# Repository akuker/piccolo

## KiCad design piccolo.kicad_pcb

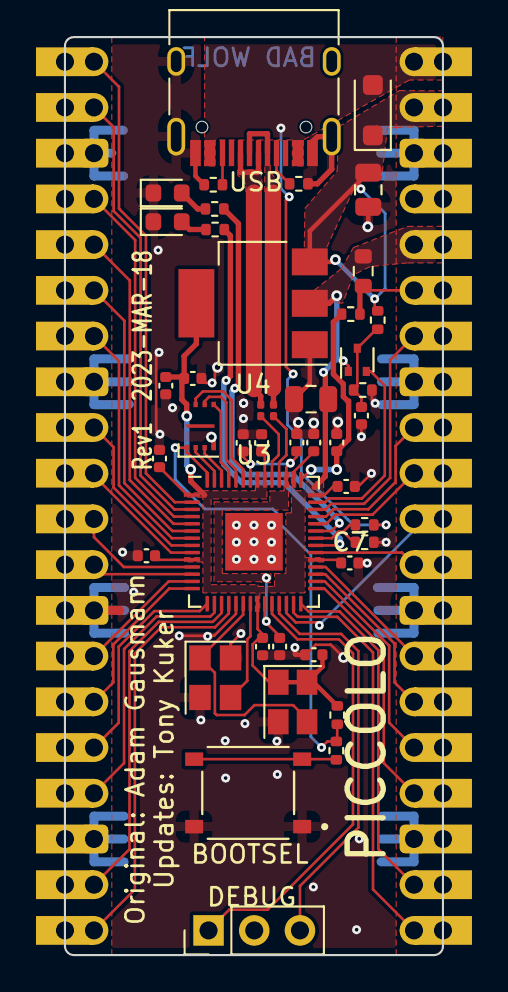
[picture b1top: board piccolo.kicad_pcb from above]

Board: 2 copper layers, 21.0 x 51.0 mm, 44 parts (0 on the bottom side), 58 nets.

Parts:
C1, C12, C14, C16: 2.2u 6.3V; C_0402_1005Metric
C2, C5, C7, C8, C9, C10, C11, C13, C15, C17: 100n 6.3V; C_0402_1005Metric
C3: 1n 25V; C_0402_1005Metric
C4, C6: 10u 6.3V; C_0805_2012Metric
D1: MBR120VLSFT1G; D_SOD-123F
D2: Green; LED_0603_1608Metric
D3: Red; LED_0603_1608Metric
J1: USB_C_Receptacle_USB2.0; USB_C_Receptacle_HRO_TYPE-C-31-M-12
J2: CON_PICO_40W; RaspberryPi_Pico_OutlineAndPads
J3: Debug; PinHeader_1x03_P2.54mm_Vertical
Q1: DMG1012T; SOT-523
R1: NO-FIT; R_0402_1005Metric
R2: 1k; R_0402_1005Metric
R3, R4: 5.1k; R_0402_1005Metric
R5: 5.6k; R_0402_1005Metric
R6: 10k; R_0402_1005Metric
R7: 200k; R_0402_1005Metric
R8: 100k; R_0402_1005Metric
R10, R11: 27R; R_0201_0603Metric
R12: 200R; R_0603_1608Metric
R13: 1R; R_0402_1005Metric
R14, R15: 470R; R_0402_1005Metric
SW2: TS-1187A-B-A-B; SW_TS-1187A-B-A-B
U1: W25Q16JVUXIQ; USON-8-1EP_3x2mm_P0.5mm_EP0.2x1.6mm
U3: RP2040; QFN-56-1EP_7x7mm_P0.4mm_EP3.2x3.2mm
U4: AMS1117-3.3; SOT-223-3_TabPin2
X1: SIT1602AI-22-33E-12.000000; Crystal_SMD_SeikoEpson_TSX3225-4Pin_3.2x2.5mm
Y1: 12MHz; Crystal_SMD_3225-4Pin_3.2x2.5mm

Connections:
+1V1: C13.1, C14.1, C15.1, U3.23 (DVDD), U3.45 (VREG_VOUT), U3.50 (DVDD)
+3V3: C1.1, C2.1, C5.1, C6.1, C7.1, C8.1, C9.1, C10.1, C11.1, C12.1, C17.1, J2.36, Q1.1 (G), R1.1, R12.1, U1.8 (VCC), U3.1 (IOVDD), U3.10 (IOVDD), U3.22 (IOVDD), U3.33 (IOVDD), U3.42 (IOVDD), U3.44 (VREG_VIN), U3.48 (USB_VDD), U3.49 (IOVDD), U4.2 (VO), X1.1 (OE), X1.4 (VDD)
/ADC_AVDD: C16.1, R13.2, U3.43 (ADC_AVDD)
/ADC_VREF: J2.35, R12.2, R13.1
/GPIO0: J2.1, U3.2 (GPIO0)
/GPIO1: J2.2, U3.3 (GPIO1)
/GPIO2: J2.4, U3.4 (GPIO2)
/GPIO3: J2.5, U3.5 (GPIO3)
/GPIO4: J2.6, U3.6 (GPIO4)
/GPIO5: J2.7, U3.7 (GPIO5)
/GPIO6: J2.9, U3.8 (GPIO6)
/GPIO7: J2.10, U3.9 (GPIO7)
/GPIO8: J2.11, U3.11 (GPIO8)
/GPIO9: J2.12, U3.12 (GPIO9)
/GPIO10: J2.14, U3.13 (GPIO10)
/GPIO11: J2.15, U3.14 (GPIO11)
/GPIO12: J2.16, U3.15 (GPIO12)
/GPIO13: J2.17, U3.16 (GPIO13)
/GPIO14: J2.19, U3.17 (GPIO14)
/GPIO15: J2.20, U3.18 (GPIO15)
/GPIO16: J2.21, U3.27 (GPIO16)
/GPIO17: J2.22, U3.28 (GPIO17)
/GPIO18: J2.24, U3.29 (GPIO18)
/GPIO19: J2.25, U3.30 (GPIO19)
/GPIO20: J2.26, U3.31 (GPIO20)
/GPIO21: J2.27, U3.32 (GPIO21)
/GPIO22: J2.29, U3.34 (GPIO22)
/GPIO23: R15.1, U3.35 (GPIO23)
/GPIO24: R5.2, R6.1, U3.36 (GPIO24)
/GPIO25: R14.1, U3.37 (GPIO25)
/GPIO26_ADC0: J2.31, U3.38 (GPIO26/ADC0)
/GPIO27_ADC1: J2.32, U3.39 (GPIO27/ADC1)
/GPIO28_ADC2: J2.34, U3.40 (GPIO28/ADC2)
/GPIO29_ADC3: Q1.2 (S), U3.41 (GPIO29/ADC3)
/QSPI_SCLK: U1.6 (CLK), U3.52 (QSPI_SCLK)
/QSPI_SD0: U1.5 (DI(IO0)), U3.53 (QSPI_SD0)
/QSPI_SD1: U1.2 (DO(IO1)), U3.55 (QSPI_SD1)
/QSPI_SD2: U1.3 (IO2), U3.54 (QSPI_SD2)
/QSPI_SD3: U1.7 (IO3), U3.51 (QSPI_SD3)
/QSPI_SS: R1.2, R2.1, U1.1 (~CS), U3.56 (QSPI_SS_N)
/RUN: J2.30, U3.26 (RUN)
/SWCLK: J3.1, U3.24 (SWCLK)
/SWDIO: J3.3, U3.25 (SWDIO)
/USB_D+: J1.A6 (D+), J1.B6 (D+), R10.1
/USB_D-: J1.A7 (D-), J1.B7 (D-), R11.1
/VSYS: C4.2, D1.1 (K), J2.39, R7.1, U4.3 (VI)
/XIN: U3.20 (XIN), X1.3 (OUT), Y1.1
/XOUT: U3.21 (XOUT), Y1.3
GND: C1.2, C2.2, C3.2, C4.1, C5.2, C6.2, C7.2, C8.2, C9.2, C10.2, C11.2, C12.2, C13.2, C14.2, C15.2, C16.2, C17.2, D2.1 (K), D3.1 (K), J1.A1 (GND), J1.A12 (GND), J1.B1 (GND), J1.B12 (GND), J1.S1 (SHIELD), J2.3, J2.8, J2.13, J2.18, J2.23, J2.28, J2.33, J2.38, J3.2, R3.1, R4.2, R6.2, R8.2, SW2.A, SW2.B, U1.4 (GND), U3.19 (TESTEN), U3.57 (GND), U4.1 (GND), X1.2 (GND), Y1.2, Y1.4
unnamed: D2.2 (A), R14.2
unnamed: D3.2 (A), R15.2
unnamed: J1.A5 (CC1), R4.1
unnamed: J1.B5 (CC2), R3.2
unnamed: C3.1, Q1.3 (D), R7.2, R8.1
unnamed: R2.2, SW2.C, SW2.D
unnamed: R11.2, U3.46 (USB_DM)
unnamed: R10.2, U3.47 (USB_DP)
VBUS: D1.2 (A), J1.A4 (VBUS), J1.A9 (VBUS), J1.B4 (VBUS), J1.B9 (VBUS), J2.40, R5.1

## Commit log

2023-03-19 value-engineered for jlcpcb
